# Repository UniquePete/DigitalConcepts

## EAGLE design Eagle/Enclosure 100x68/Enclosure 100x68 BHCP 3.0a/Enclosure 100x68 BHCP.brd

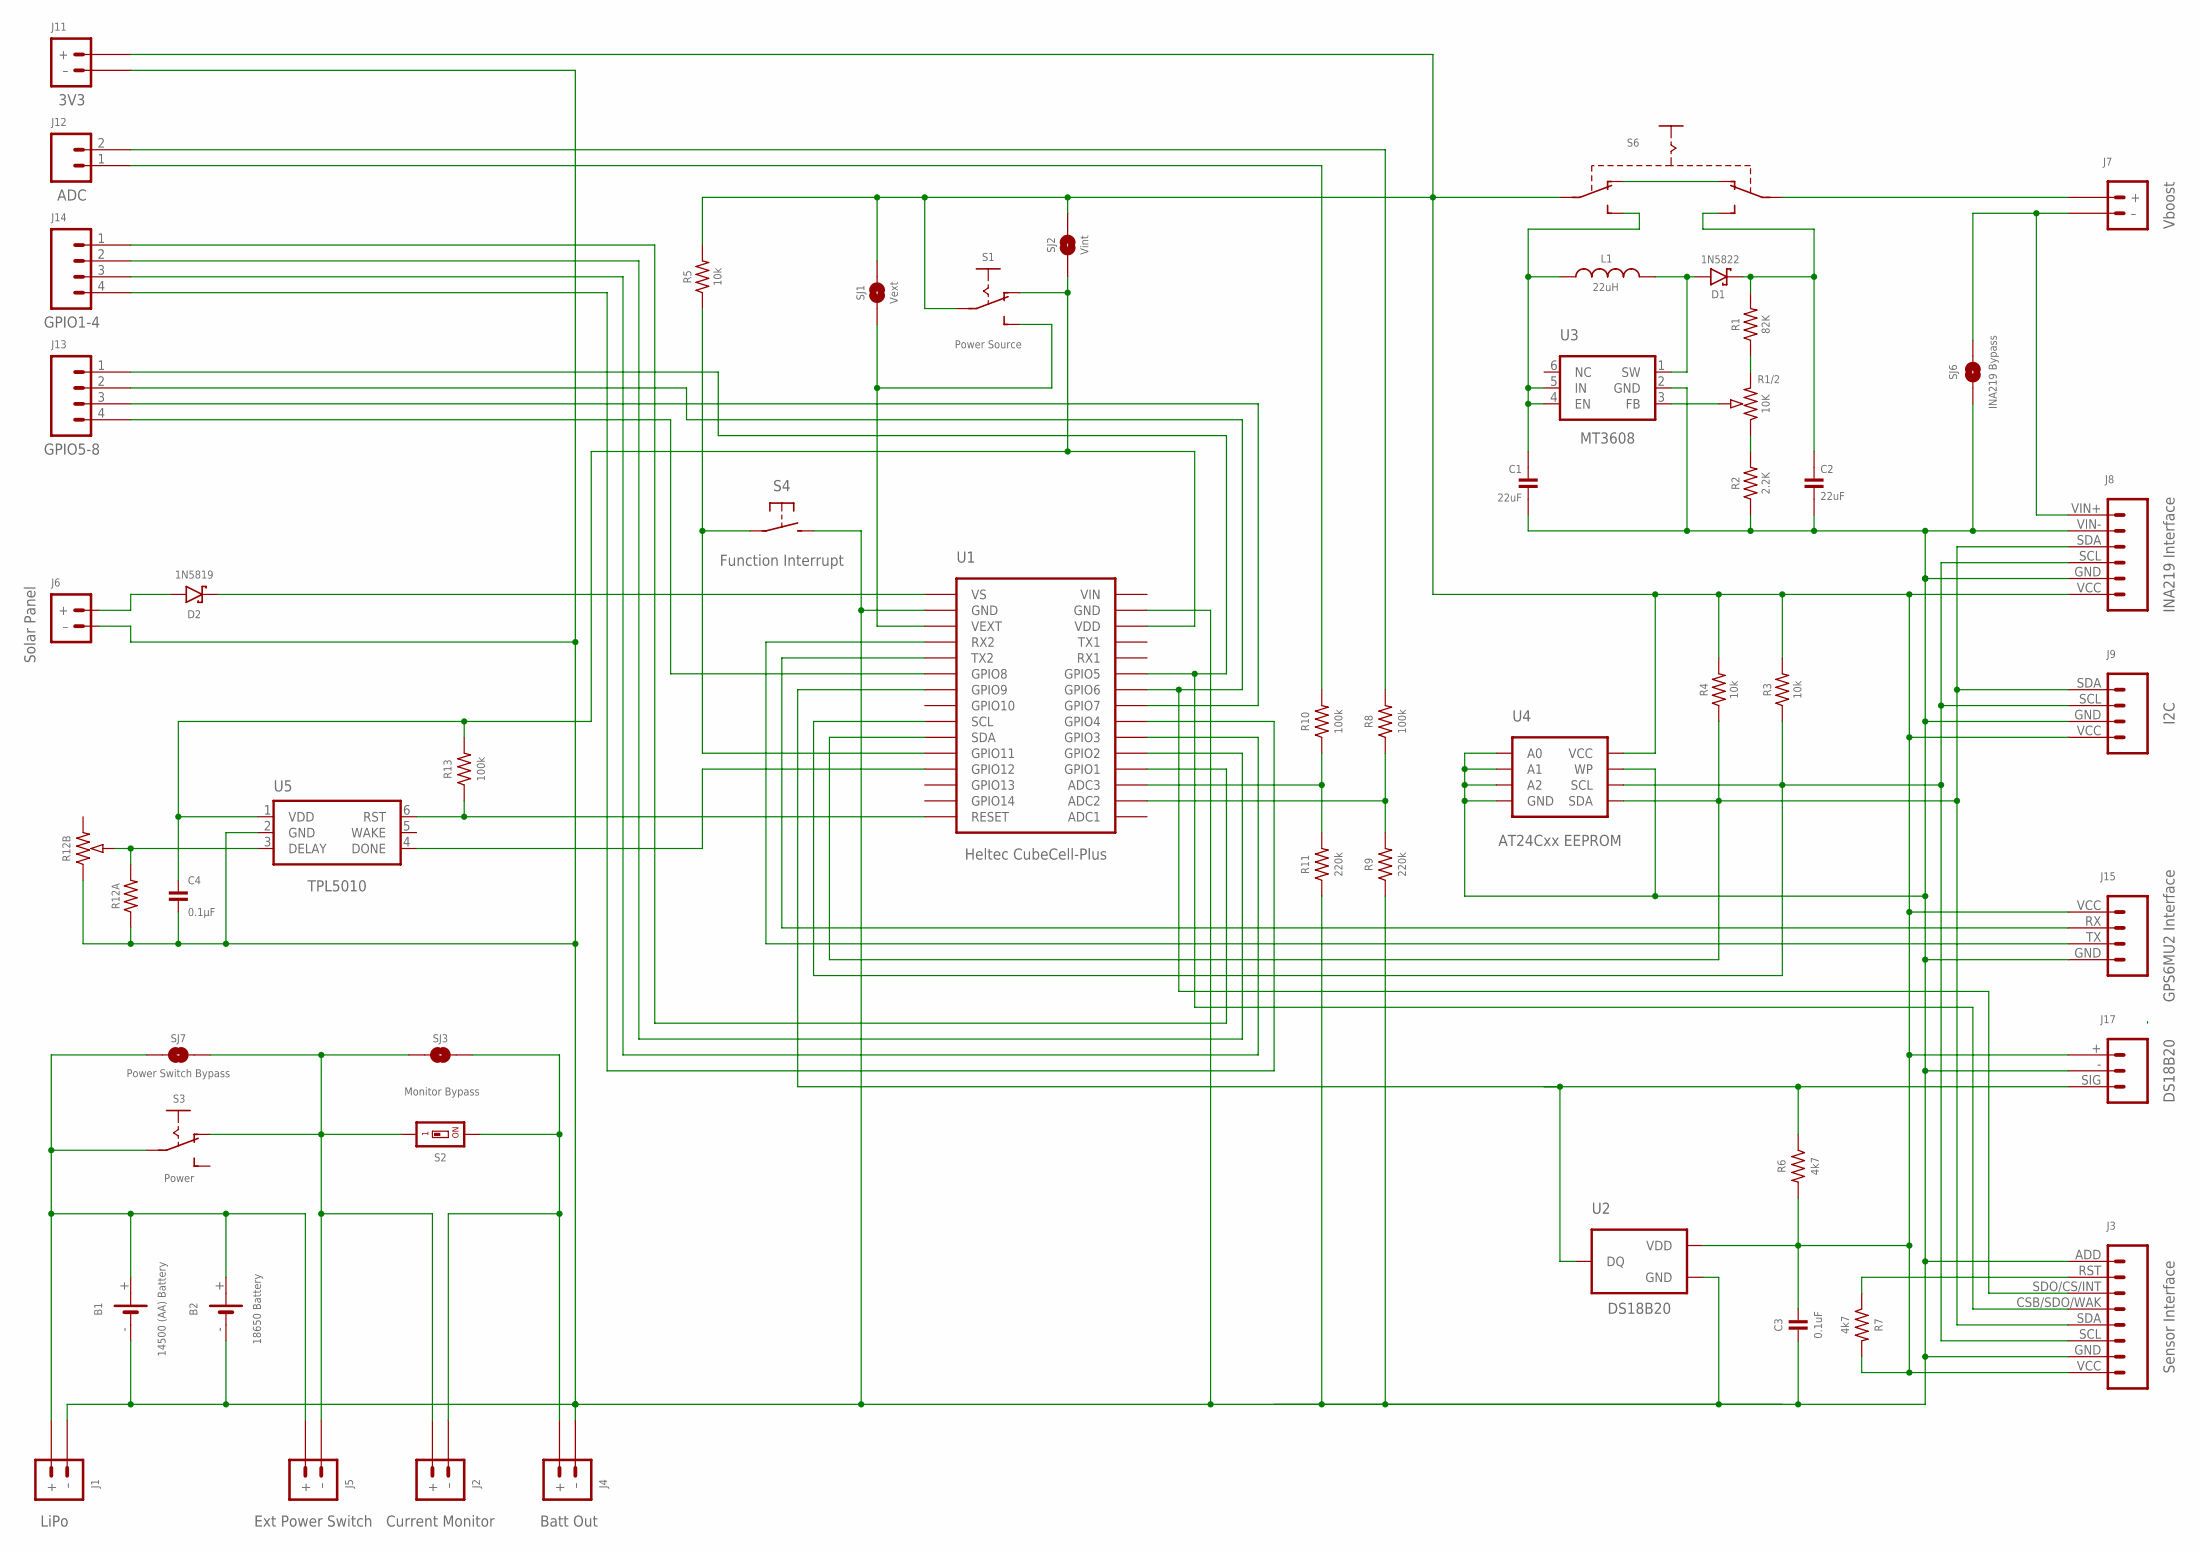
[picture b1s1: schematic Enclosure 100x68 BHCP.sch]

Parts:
B1: 14500 (AA) Battery; BATTERY-14500
B2: 18650 Battery; BATTERY-18650
C1, C2: 22uF; C1206
C3: 0.1uF; C0805
C4: 0.1µF; C0805
D1: 1N5822; DIODE_SMB
D2: 1N5819; SOD-123
J1: LiPo; JST-PH2.0-2-HORIZONTAL-POWER
J2: Current Monitor; JST-PH2.0-2-HORIZONTAL-POWER
J3: Sensor Interface; CONN_08-SENSOR
J4: Batt Out; JST-GH1.25-2-HORIZONTAL
J5: Ext Power Switch; JST-PH2.0-2-DUAL-POWER
J6: Solar Panel; JST-PH2.0-2-VERTICAL=POWER
J7: Vboost; JST-PH2.0-2-HORIZONTAL-POWER
J8: INA219 Interface; CONN_06-INA219
J9: I2C; JST-PH2.0-4-HORIZONTAL@1
J11: 3V3; JST-PH2.0-2-HORIZONTAL-POWER
J12: ADC; JST-PH2.0-2-HORIZONTAL
J13: GPIO5-8; JST-PH2.0-4-HORIZONTAL
J14: GPIO1-4; JST-PH2.0-4-HORIZONTAL
J15: GPS6MU2 Interface; CONN_04-GPS
J17: DS18B20; JST-PH2.0-DS18B20-HORIZONTAL
L1: 22uH; CDRH104R+6D28
R1: 82K; R0805
R1/2: 10K; RTRIM64P
R2: 2.2K; R0805
R3, R4, R5: 10k; R0805
R6, R7: 4k7; R0805
R8, R10, R13: 100k; R0805
R9, R11: 220k; R0805
R12A: RESISTORR0805; R0805
R12B: RESISTOR-TRIMM-33-US; RTRIM3*3
S1: Power Source; SWITCH-SPDT-SMT
S2: Monitor Bypass; SMD-001
S3: Power; SWITCH-SPDT-PTH
S4: Function Interrupt; SWITCH-2-PAD
S6: SWITCH-SLIDE-DPDT-PTH-S; SWITCH-DPDT-PTH
SJ1: Vext; SJ
SJ2: Vint; SJ-VIA-12
SJ3: Monitor; SJ
SJ6: INA219 Bypass; SJ
SJ7: Power Switch Bypass; SJ
U1: Heltec CubeCell-Plus; HELTEC-CUBECELL=PLUS-X
U2: DS18B20; TO-92
U3: MT3608; SOT-23-6
U4: AT24Cxx EEPROM; SOP-8
U5: TPL5010; SOT-23-6

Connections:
GND: B1.-, B2.-, C1.2, C2.2, C3.2, C4.2, J1.- (–), J3.ADD (8), J3.GND (2), J4.- (–), J6.- (–), J8.GND (2), J8.VIN- (5), J9.GND (2), J11.- (–), J15.GND (1), J17.- (2), R2.1, R9.1, R11.1, R12A.1, R12B.1 (A), S4.P$2 (S), SJ6.1, U1.GND@14 (GND), U1.GND@17 (GND), U2.1 (GND), U3.2 (GND), U4.P$1 (A0), U4.P$2 (A1), U4.P$3 (A2), U4.P$4 (GND), U4.P$7 (WP), U5.2 (GND)
unnamed: D2.A, J6.+
unnamed: R10.1, R11.2, U1.ADC3
unnamed: J2.- (–), J4.+, S2.2, SJ3.1
unnamed: B1.+, B2.+, J1.+, J5.+, S3.2, SJ7.2
unnamed: D2.C, U1.VS
unnamed: D1.A, L1.1, U3.1 (SW)
unnamed: J12.1, R10.2
unnamed: J3.SCL (3), J8.SCL (3), J9.SCL (3), R3.1, U1.SCL, U4.P$6 (SCL)
unnamed: J3.RST (7), R7.1
unnamed: J3.CSB/SDO/WAK (5), J13.1 (4), U1.GPIO5
unnamed: J3.SDA (4), J8.SDA (4), J9.SDA (4), R4.1, U1.SDA, U4.P$5 (SDA)
unnamed: J13.4 (1), U1.GPIO8
unnamed: S1.3 (S), SJ1.1, U1.VEXT
unnamed: J15.RX (3), U1.TX2
unnamed: J7.- (–), J8.VIN+ (6), SJ6.2
unnamed: J15.TX (2), U1.RX2
unnamed: R12A.2, R12B.2 (S), U5.3 (DELAY)
unnamed: J3.SDO/CS/INT (6), J13.2 (3), U1.GPIO6
unnamed: J7.+, S6.P$2 (P1)
unnamed: J2.+, J5.- (–), S2.1, S3.1 (O), SJ3.2, SJ7.1
unnamed: R1/2.2 (S), U3.3 (FB)
unnamed: R1/2.1 (A), R2.2
unnamed: J17.SIG (1), R6.1, U1.GPIO9, U2.2 (DQ)
unnamed: C1.1, L1.2, S6.P$6 (S2), U3.4 (EN), U3.5 (IN)
unnamed: S6.P$1 (O1), S6.P$4 (O2)
unnamed: R5.1, S4.P$1, U1.GPIO11
unnamed: C2.1, D1.C, R1.2, S6.P$3 (S1)
unnamed: J14.1 (4), U1.GPIO1
unnamed: J14.2 (3), U1.GPIO2
unnamed: J12.2, R8.2
unnamed: R8.1, R9.2, U1.ADC2
unnamed: R13.1, U1.RST (RESET), U5.6 (RST)
unnamed: J14.3 (2), U1.GPIO3
unnamed: J14.4 (1), U1.GPIO4
unnamed: U1.GPIO12, U5.4 (DONE)
unnamed: R1.1, R1/2.3 (E)
unnamed: C4.1, R13.2, S1.1 (O), SJ2.1, SJ2.1@V (1), U1.VDD, U5.1 (VDD)
unnamed: J13.3 (2), U1.GPIO7
VEXT: C3.1, J3.VCC (1), J8.VCC (1), J9.VCC (1), J11.+, J15.VCC (4), J17.+ (3), R3.2, R4.2, R5.2, R6.2, R7.2, S1.2, S6.P$5 (P2), SJ1.2, SJ2.2, SJ2.2@V (2), U2.3 (VDD), U4.P$8 (VCC)
VIN: U1.VIN

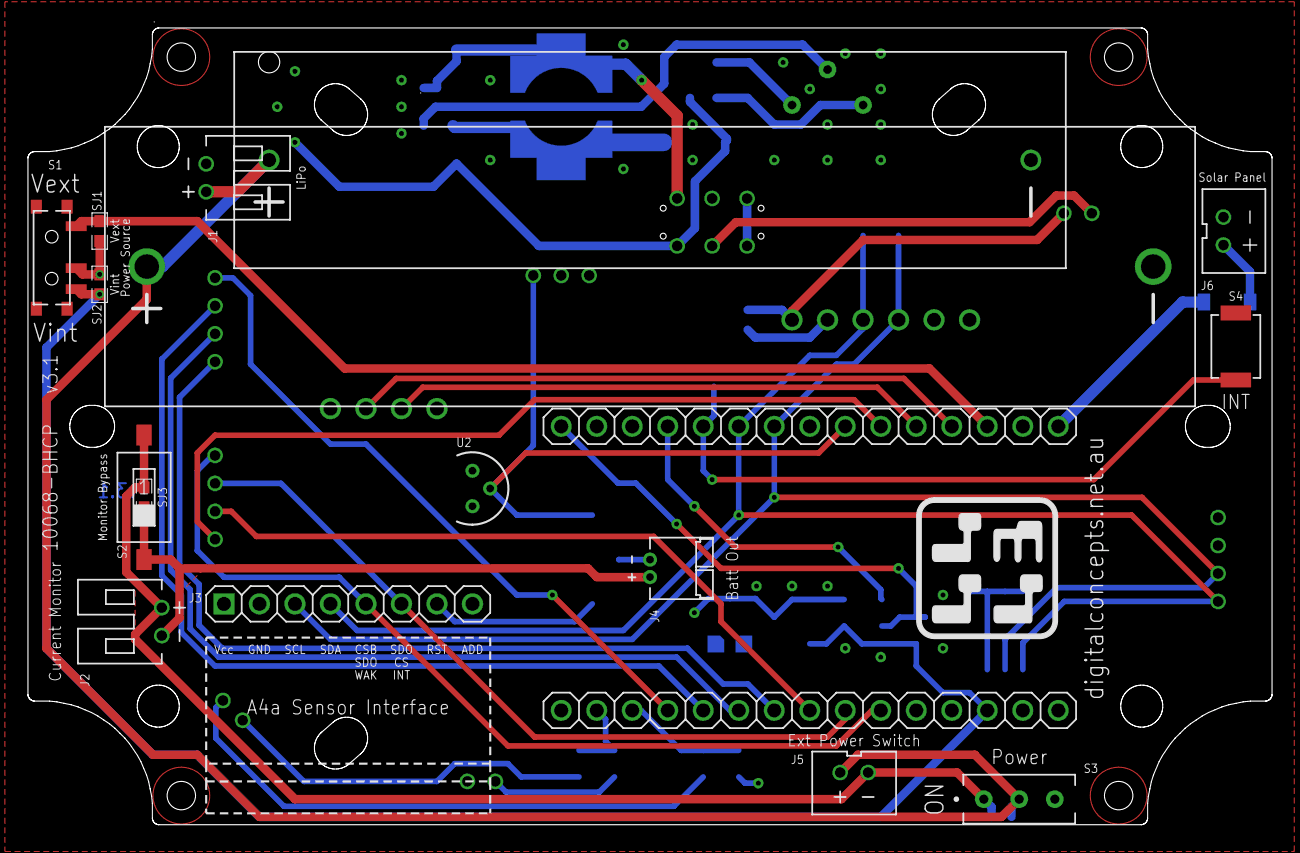
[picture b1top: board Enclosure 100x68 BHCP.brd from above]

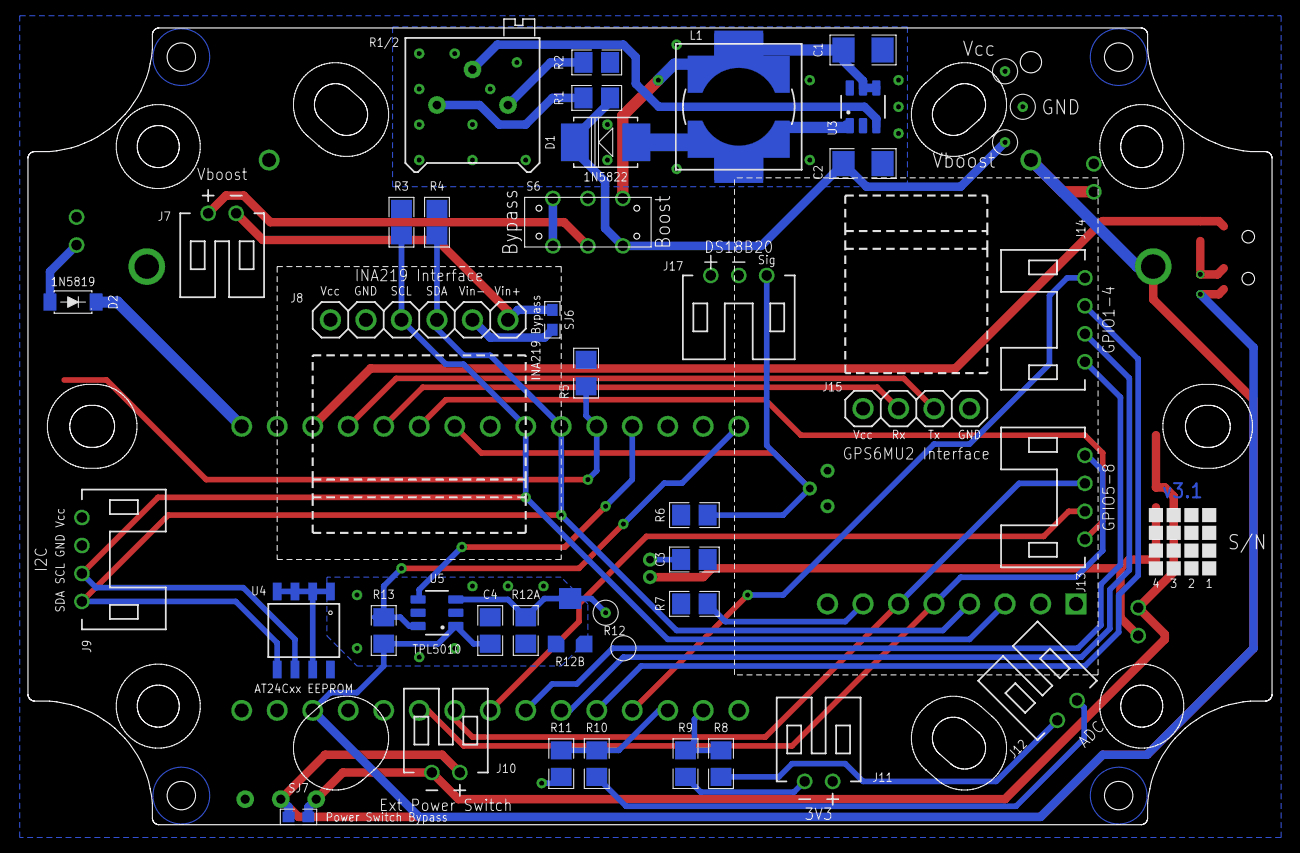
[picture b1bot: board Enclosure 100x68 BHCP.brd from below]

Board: 2 copper layers, 89.0 x 57.0 mm, 54 parts (38 on the bottom side), 40 nets.

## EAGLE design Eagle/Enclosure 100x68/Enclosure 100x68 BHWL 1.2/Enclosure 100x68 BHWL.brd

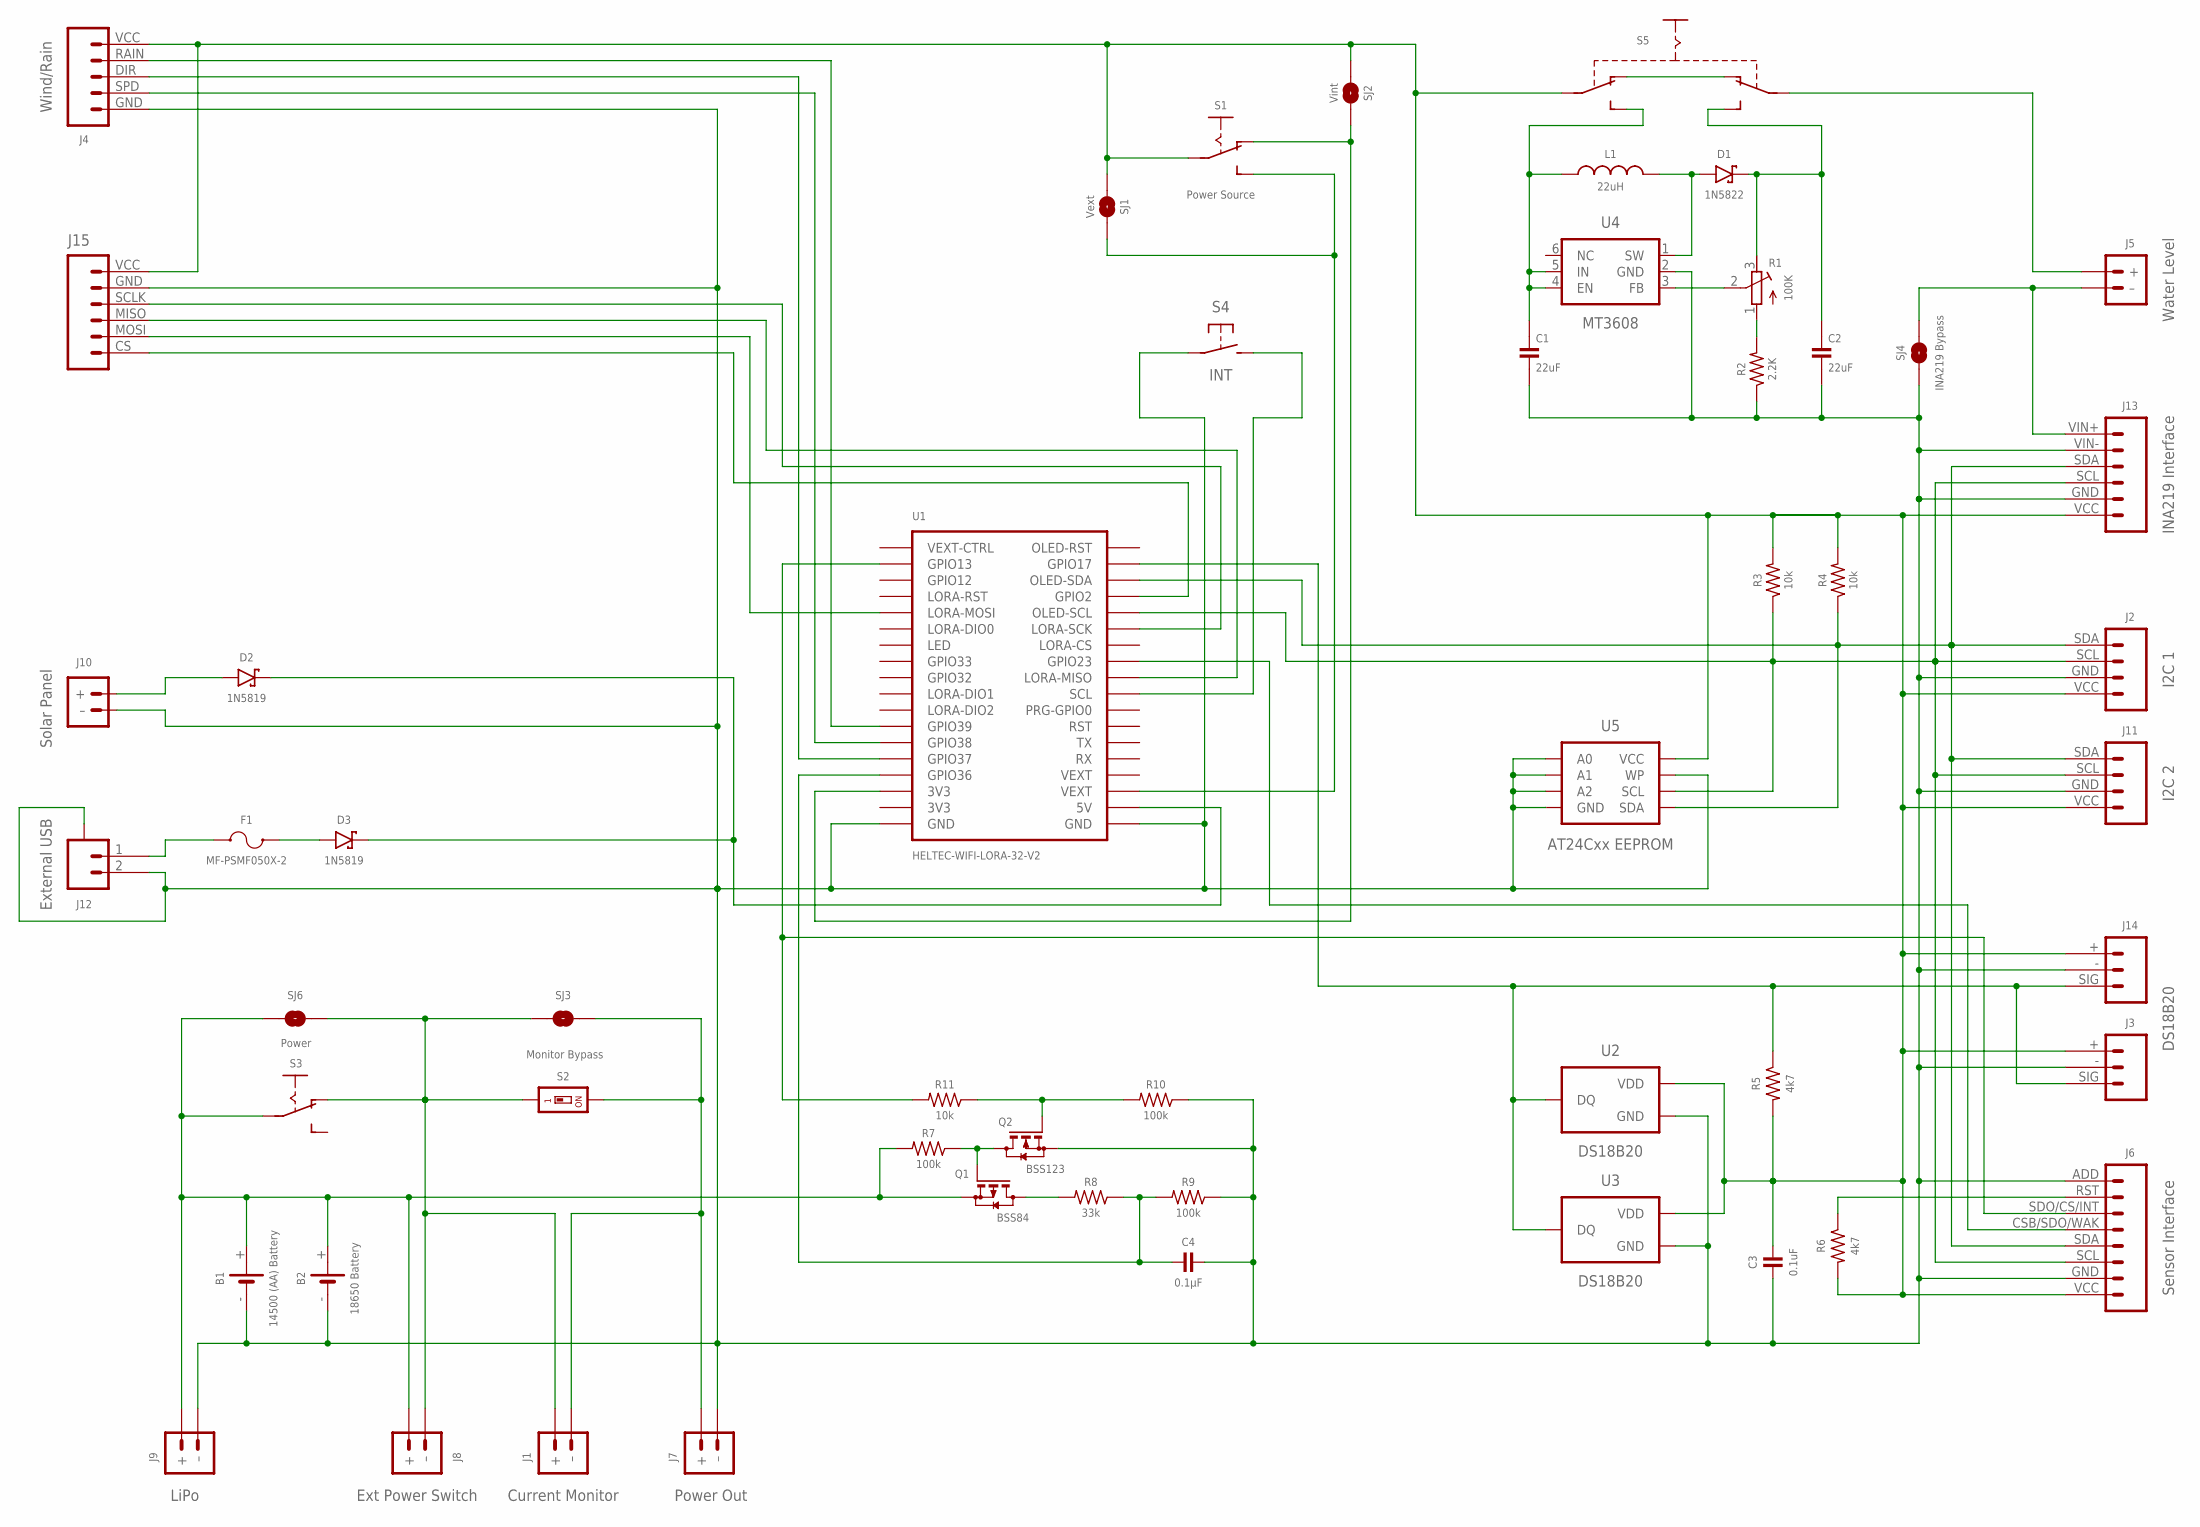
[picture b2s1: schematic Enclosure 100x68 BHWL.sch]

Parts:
B1: 14500 (AA) Battery; BATTERY-14500
B2: 18650 Battery; BATTERY-18650
C1, C2: 22uF; C1206
C3: 0.1uF; C0805
C4: 0.1µF; C0805
D1: 1N5822; DIODE_SMB
D2, D3: 1N5819; SOD-123
F1: MF-PSMF050X-2; F0805
J1: Current Monitor; JST-PH2.0-2-HORIZONTAL
J2: I2C 1; JST-PH2.0-4-VERTICAL-I2C
J3: DS18B20; JST-PH2.0-3-VERTICAL-SIG
J4: Wind/Rain; JST-PH2.0-5-DUAL-WEATHER
J5: Water Level; JST-PH2.0-2-DUAL-POWER
J6: Sensor Interface; CONN_08-SENSOR
J7: Power Out; JST-GH1.25-2-HORIZONTAL
J8: Ext Power Switch; JST-PH2.0-2-DUAL-POWER
J9: LiPo; JST-PH2.0-2-HORIZONTAL-POWER
J10: Solar Panel; JST-PH2.0-2-VERTICAL=POWER
J11: I2C 2; JST-PH2.0-4-HORIZONTAL
J12: External USB; JST-SH1.0-2-HORIZONTAL
J13: INA219 Interface; CONN_06-INA219
J14: JST-PH2.0-3-HORIZONTAL-DS18B20; JST-PH2.0-DS18B20-HORIZONTAL
J15: JST-PH2.0-6-HORIZONTAL-SPI
L1: 22uH; CDRH104R+6D28
Q1: BSS84; SOT23-3
Q2: BSS123; SOT23-3
R1: 100K; RTRIM64P
R2: 2.2K; R0805
R3, R4, R11: 10k; R0805
R5, R6: 4k7; R0805
R7, R9, R10: 100k; R0805
R8: 33k; R0805
S1: Power Source; SWITCH-SPDT-SMT
S2: Monitor Bypass; SMD-001
S3: Power; SWITCH-SPDT-PTH
S4: INT; SWITCH-2-PAD
S5: SWITCH-SLIDE-DPDT-PTH-S; SWITCH-DPDT-PTH
SJ1: Vext; SJ
SJ2: Vint; SJ-VIA-2
SJ3: Monitor; SJ
SJ4: INA219 Bypass; SJ
SJ6: Power; SJ
U1: HELTEC-WIFI-LORA-32-V2
U2, U3: DS18B20; TO-92
U4: MT3608; SOT-23-6
U5: AT24Cxx EEPROM; SOP-8

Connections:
GND: B1.-, B2.-, C1.2, C2.2, C3.2, C4.2, J2.GND (3), J3.- (2), J4.GND (5), J6.ADD (8), J6.GND (2), J7.- (–), J9.- (–), J10.- (–), J11.GND (2), J12.2, J12.A@1 (A), J12.A@2 (A), J13.GND (2), J13.VIN- (5), J14.- (2), J15.GND (5), Q2.2 (S), R2.1, R9.1, R10.1, S4.P$1, SJ4.1, U1.GND@1 (GND), U1.GND@36 (GND), U2.1 (GND), U3.1 (GND), U4.2 (GND), U5.P$1 (A0), U5.P$2 (A1), U5.P$3 (A2), U5.P$4 (GND), U5.P$7 (WP)
unnamed: D2.A, J10.+
unnamed: J4.RAIN (2), U1.GPIO39
unnamed: J6.CSB/SDO/WAK (5), U1.GPIO23
unnamed: J2.SCL (2), J6.SCL (3), J11.SCL (3), J13.SCL (3), R3.1, U1.GPIO15 (OLED-SCL), U5.P$6 (SCL)
unnamed: D2.C, D3.C, U1.5V
unnamed: D1.A, L1.1, U4.1 (SW)
unnamed: Q1.3 (D), R8.2
unnamed: J1.2 (–), J7.+, S2.2, SJ3.1
unnamed: J6.RST (7), R6.1
unnamed: J4.DIR (3), U1.GPIO37
unnamed: J2.SDA (1), J6.SDA (4), J11.SDA (4), J13.SDA (4), R4.1, U1.GPIO4 (OLED-SDA), U5.P$5 (SDA)
unnamed: J4.SPD (4), U1.GPIO38
unnamed: S1.3 (S), SJ1.1, U1.VEXT@3 (VEXT)
unnamed: F1.2, J12.1
unnamed: J5.- (–), J13.VIN+ (6), SJ4.2
unnamed: D3.A, F1.1
unnamed: S4.P$2 (S), U1.GPIO22 (SCL)
unnamed: C4.1, R8.1, R9.2, U1.GPIO36
unnamed: S1.1 (O), SJ2.1, U1.3V3@34 (3V3)
unnamed: J5.+, S5.P$2 (P1)
unnamed: J1.1 (+), J8.- (–), S2.1, S3.1 (O), SJ3.2, SJ6.1
unnamed: R1.2 (S), U4.3 (FB)
unnamed: R1.1 (A), R2.2
unnamed: J3.SIG (1), J14.SIG (1), R5.1, U1.GPIO17, U2.2 (DQ), U3.2 (DQ)
unnamed: C1.1, L1.2, S5.P$6 (S2), U4.4 (EN), U4.5 (IN)
unnamed: S5.P$1 (O1), S5.P$4 (O2)
unnamed: J15.SCLK (4), U1.GPIO5 (LORA-SCK)
unnamed: C2.1, D1.C, R1.3 (E), S5.P$3 (S1)
unnamed: J15.MOSI (2), U1.GPIO27 (LORA-MOSI)
unnamed: B1.+, B2.+, J8.+, J9.+, Q1.2 (S), R7.2, S3.2, SJ6.2
unnamed: J15.MISO (3), U1.GPIO19 (LORA-MISO)
unnamed: J6.SDO/CS/INT (6), R11.2, U1.GPIO13
unnamed: J15.CS (1), U1.GPIO2
unnamed: Q1.1 (G), Q2.3 (D), R7.1
unnamed: Q2.1 (G), R10.2, R11.1
VEXT: C3.1, J2.VCC (4), J3.+ (3), J4.VCC (1), J6.VCC (1), J11.VCC (1), J13.VCC (1), J14.+ (3), J15.VCC (6), R3.2, R4.2, R5.2, R6.2, S1.2, S5.P$5 (P2), SJ1.2, SJ2.2, SJ2.2@V (2), U2.3 (VDD), U3.3 (VDD), U5.P$8 (VCC)

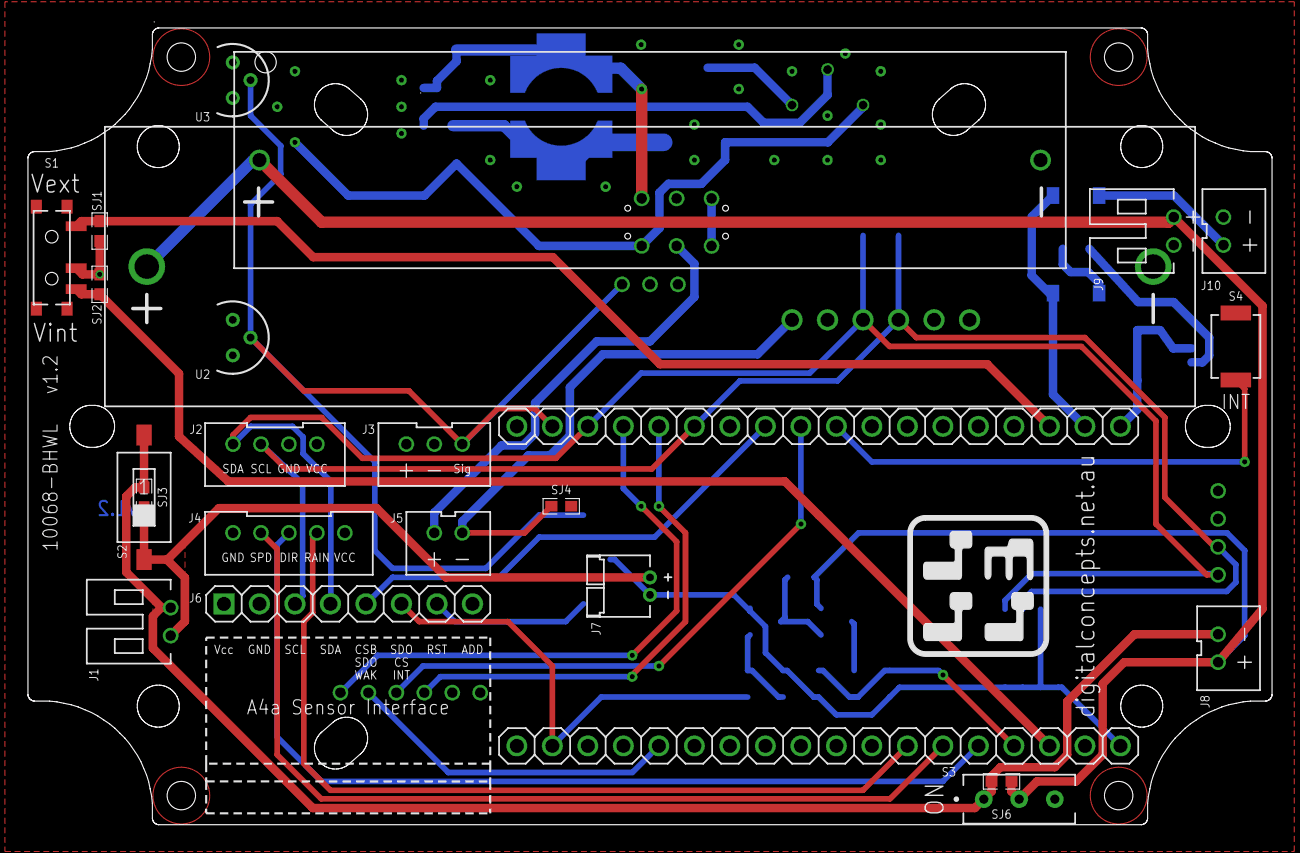
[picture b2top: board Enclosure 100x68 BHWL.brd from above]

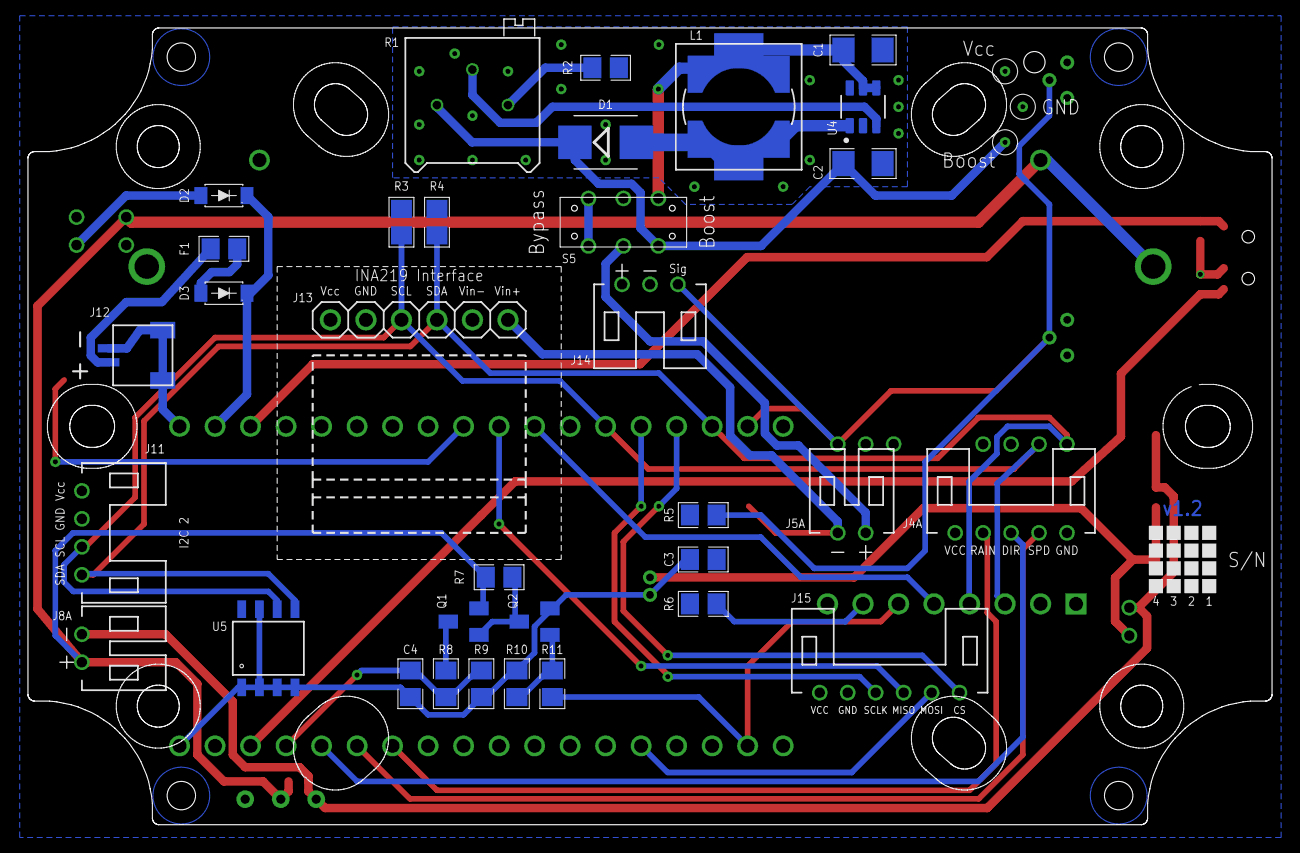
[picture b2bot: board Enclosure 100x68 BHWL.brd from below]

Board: 2 copper layers, 89.0 x 57.0 mm, 54 parts (33 on the bottom side), 37 nets.

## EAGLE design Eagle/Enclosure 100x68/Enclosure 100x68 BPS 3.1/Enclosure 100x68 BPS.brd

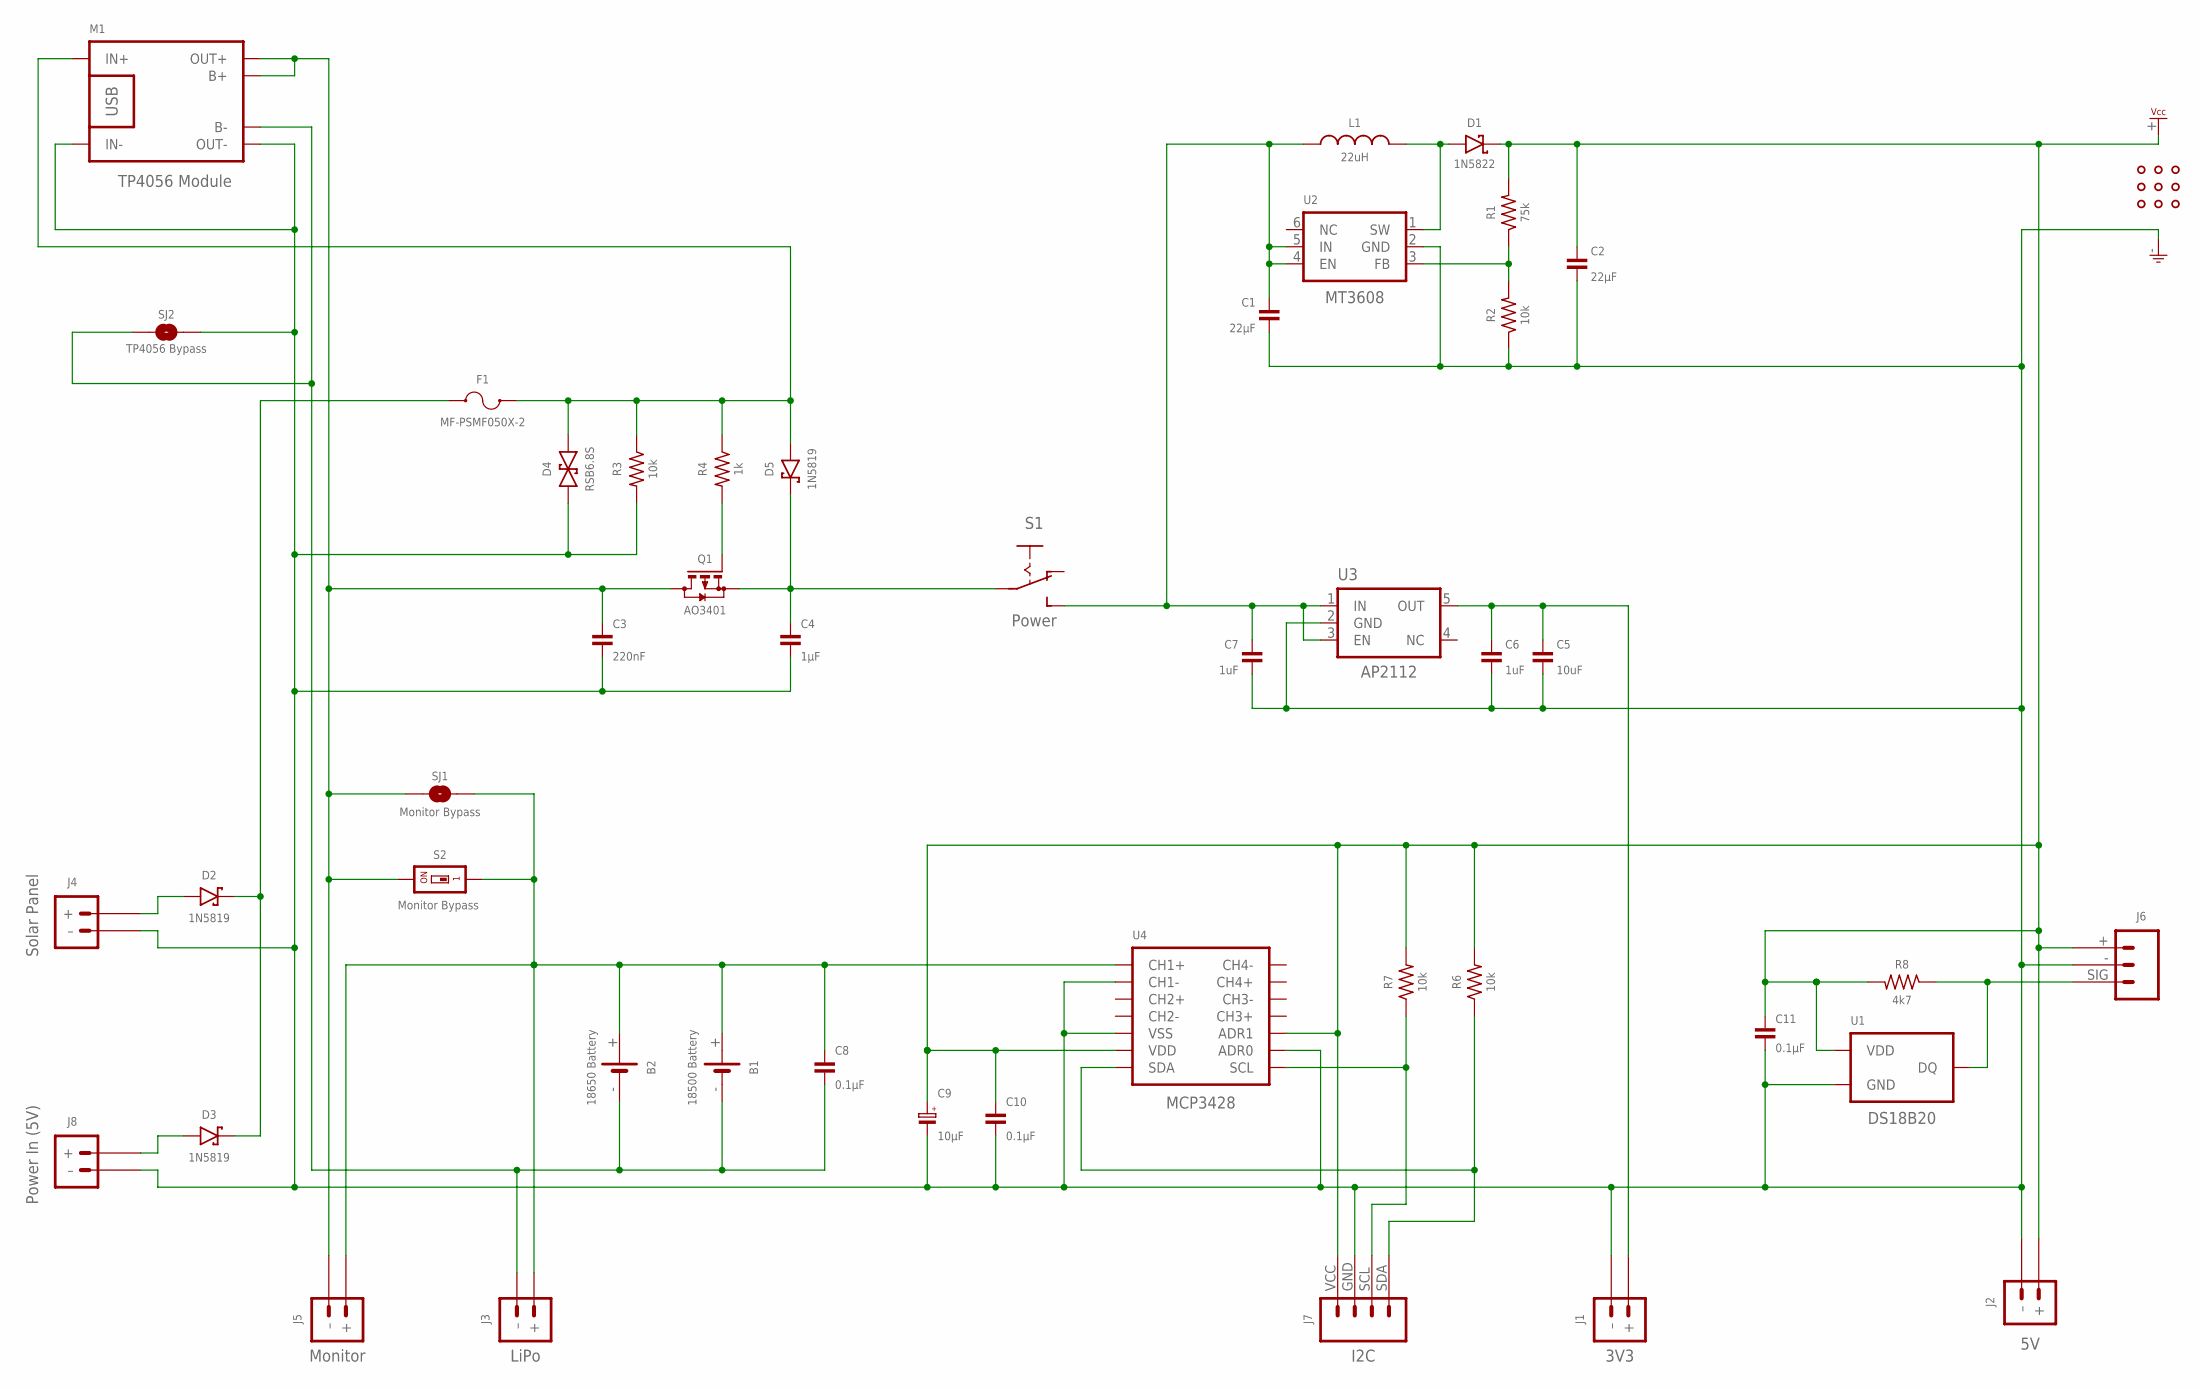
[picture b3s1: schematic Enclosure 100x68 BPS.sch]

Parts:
B1: 18500 Battery; BATTERY-18500
B2: 18650 Battery; BATTERY-18650
C1, C2: 22µF; C1206
C3: 220nF; C0805
C4: 1µF; C0805
C5: 10uF; C0805
C6, C7: 1uF; C0805
C8, C10, C11: 0.1µF; C0805
C9: 10µF; C1206-POLARISED
D1: 1N5822; DIODE_SMB
D2, D3, D5: 1N5819; SOD-123
D4: RSB6.8S; EMD2
F1: MF-PSMF050X-2; F0805
J1: 3V3; JST-PH2.0-2-VERTICAL-POWER
J2: 5V; JST-PH2.0-2-VERTICAL-POWER
J3: LiPo; JST-PH2.0-2-HORIZONTAL-POWER
J4: Solar Panel; JST-PH2.0-2-VERTICAL-POWER
J5: Monitor; JST-PH2.0-2-VERTICAL-POWER
J6: JST-PH2.0-3-HORIZONTAL-DS18B20
J7: I2C; JST-PH2.0-4-HORIZONTAL-I2C
J8: Power In (5V); JST-GH1.25-2-HORIZONTAL
L1: 22uH; CDRH104R+
M1: TP4056 Module; BATTERY-CHARGER-LI-PROT
Q1: AO3401; SOT-23
R1: 75k; R0805
R2, R3, R6, R7: 10k; R0805
R4: 1k; R0805
R8: 4k7; R0805
S1: Power; SWITCH-SPDT-PTH
S2: Monitor Bypass; SMD-001-VIA-1
SJ1: Monitor Bypass; SJ
SJ2: TP4056 Bypass; SJ
U1: DS18B20; TO-92
U2: MT3608; SOT-23-6
U3: AP2112; SOT25
U4: MCP3428; SOIC-14
U$1: PROTO-34X22-PI-CUT

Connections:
3V3: C5.1, C6.1, J1.+, U3.5 (OUT)
5V: C2.1, C9.1 (+), C10.1, C11.1, D1.C, J2.+, J6.+ (3), J7.VCC (1), R1.2, R6.2, R7.2, R8.2, U1.3 (VDD), U4.P$6 (VDD), U4.P$10 (ADR1), U$1.+ (VCC)
GND: C1.2, C2.2, C3.2, C4.2, C5.2, C6.2, C7.2, C9.2 (-), C10.2, C11.2, D4.P$2 (2), J1.- (–), J2.- (–), J4.- (–), J6.- (2), J7.GND (2), J8.- (–), M1.IN-, M1.OUT-, R2.1, R3.2, SJ2.1, U1.1 (GND), U2.2 (GND), U3.2 (GND), U4.P$2 (CH1-), U4.P$5 (VSS), U4.P$9 (ADR0), U$1.- (GND)
unnamed: D2.A, J4.+
unnamed: C1.1, C7.1, L1.2, S1.3 (S), U2.4 (EN), U2.5 (IN), U3.1 (IN), U3.3 (EN)
unnamed: R1.1, R2.2, U2.3 (FB)
unnamed: J7.SCL (3), R7.1, U4.P$8 (SCL)
unnamed: D1.A, L1.1, U2.1 (SW)
unnamed: D4.P$1 (1), D5.A, F1.2, M1.IN+, R3.1, R4.1
unnamed: C4.1, D5.C, Q1.2 (S), S1.2
unnamed: B1.+, B2.+, C8.1, J3.+, J5.+, S2.1, S2.1@VIA (1), SJ1.1, U4.P$1 (CH1+)
unnamed: D3.A, J8.+
unnamed: J6.SIG (1), R8.1, U1.2 (DQ)
unnamed: J7.SDA (4), R6.1, U4.P$7 (SDA)
unnamed: Q1.1 (G), R4.2
unnamed: C3.1, J5.- (–), M1.B+, M1.OUT+, Q1.3 (D), S2.2, SJ1.2
unnamed: B1.-, B2.-, C8.2, J3.- (–), M1.B-, SJ2.2
unnamed: D2.C, D3.C, F1.1

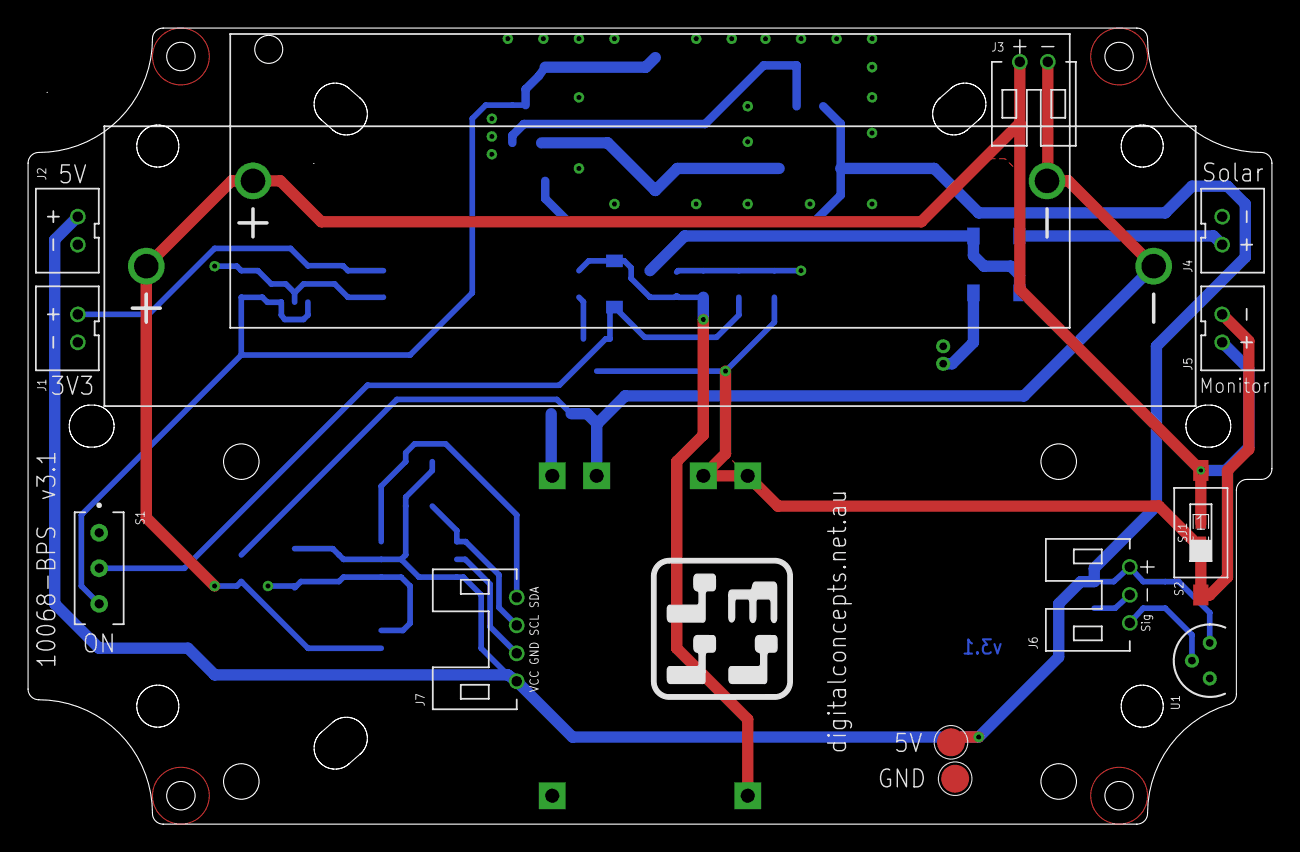
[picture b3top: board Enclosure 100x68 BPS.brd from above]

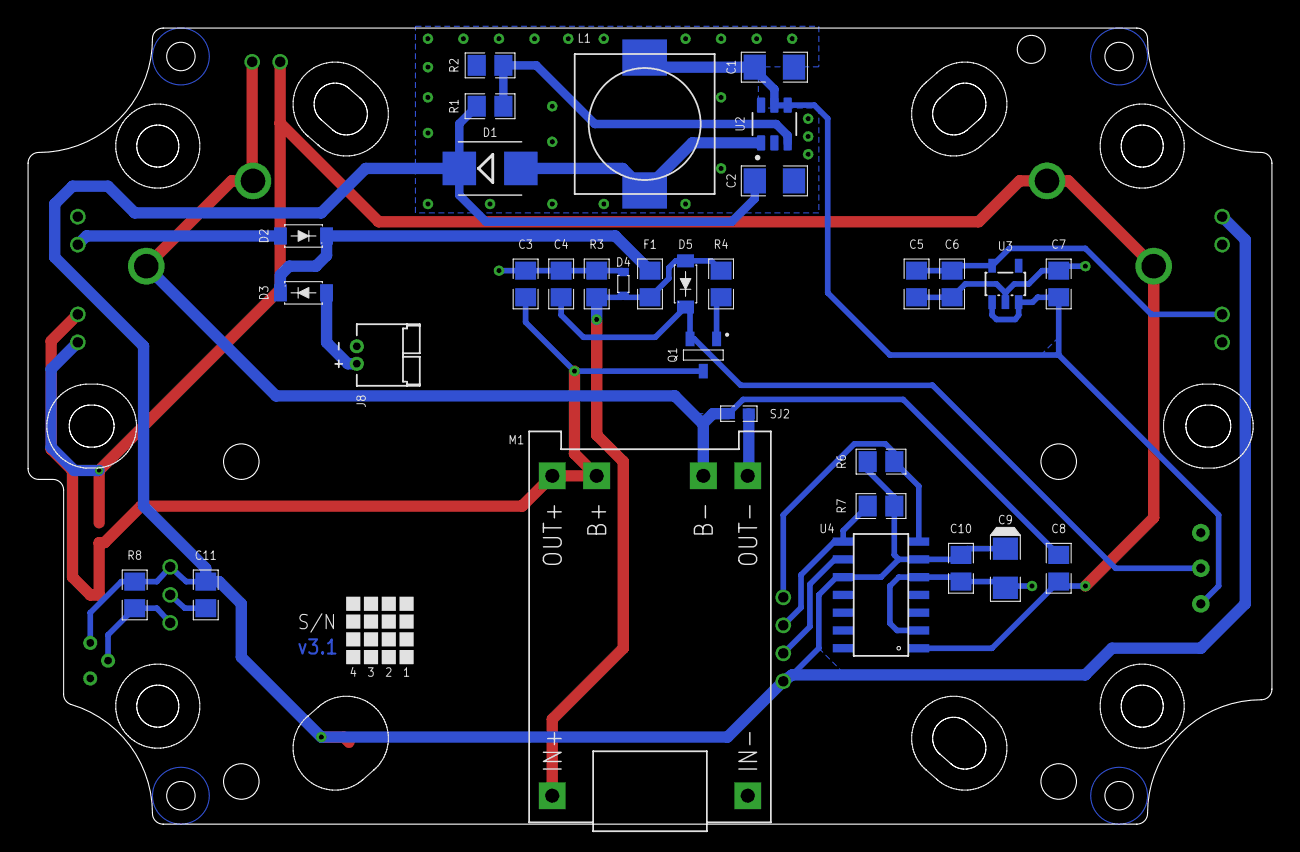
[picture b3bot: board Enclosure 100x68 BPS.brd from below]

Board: 2 copper layers, 88.9 x 56.9 mm, 46 parts (32 on the bottom side), 18 nets.
